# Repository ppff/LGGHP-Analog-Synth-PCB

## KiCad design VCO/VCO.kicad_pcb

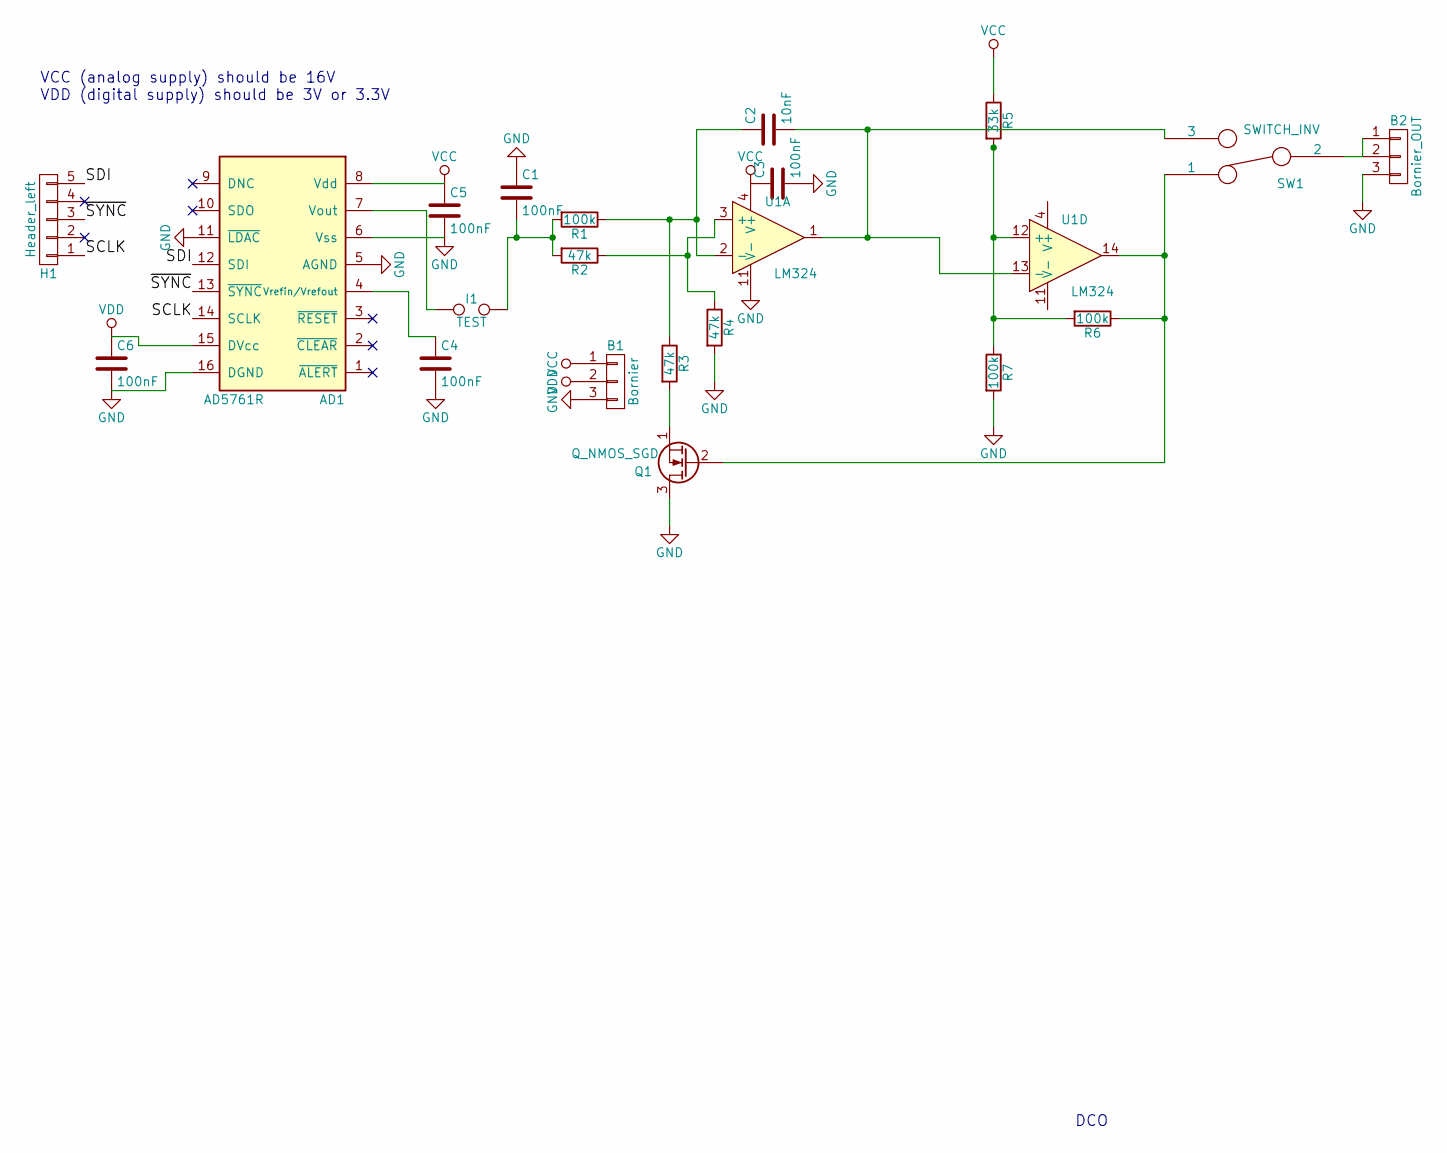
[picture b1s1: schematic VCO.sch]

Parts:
AD1: AD5761R; TSSOP-16_4.4x5mm_Pitch0.65mm
B1: Bornier; Bornier_3pins
B2: Bornier_OUT; Bornier_3pins
C1, C3, C4, C5, C6: 100nF; C_Axial_L5.1mm_D3.1mm_P7.50mm_Horizontal
C2: 10nF; C_Axial_L5.1mm_D3.1mm_P7.50mm_Horizontal
H1: Header_left; Pin_Header_Straight_1x05_Pitch2.54mm
I1: TEST; test
Q1: Q_NMOS_SGD; TO-92_Inline_Wide
R1, R6, R7: 100k; R_Axial_DIN0207_L6.3mm_D2.5mm_P7.62mm_Horizontal
R2, R3, R4: 47k; R_Axial_DIN0207_L6.3mm_D2.5mm_P7.62mm_Horizontal
R5: 33k; R_Axial_DIN0207_L6.3mm_D2.5mm_P7.62mm_Horizontal
SW1: SWITCH_INV; switch
U1: LM324; DIP-14_W7.62mm

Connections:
/SCLK: AD1.14 (SCLK), H1.1
/SDI: AD1.12 (SDI), H1.5
/~SYNC: AD1.13 (~SYNC), H1.3
GND: AD1.5 (AGND), AD1.6 (Vss), AD1.11 (~LDAC), AD1.16 (DGND), B1.3, B2.3, C1.1, C3.2, C4.2, C5.2, C6.2, Q1.3 (D), R4.2, R7.2, U1.11 (V-)
unnamed: AD1.4 (Vrefin/Vrefout), C4.1
unnamed: AD1.7 (Vout), I1.1
unnamed: B2.1, B2.2, SW1.2
unnamed: C1.2, I1.2, R1.2, R2.2
unnamed: C2.1, R1.1, R3.1, U1.2 (-)
unnamed: C2.2, SW1.3, U1.1, U1.13 (-)
unnamed: Q1.1 (S), R3.2
unnamed: Q1.2 (G), R6.1, SW1.1, U1.14
unnamed: R2.1, R4.1, U1.3 (+)
unnamed: R5.2, R6.2, R7.1, U1.12 (+)
VCC: AD1.8 (Vdd), B1.1, C3.1, C5.1, R5.1, U1.4 (V+)
VDD: AD1.15 (DVcc), B1.2, C6.1

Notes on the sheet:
DCO
VCC (analog supply) should be 16V VDD (digital supply) should be 3V or 3.3V

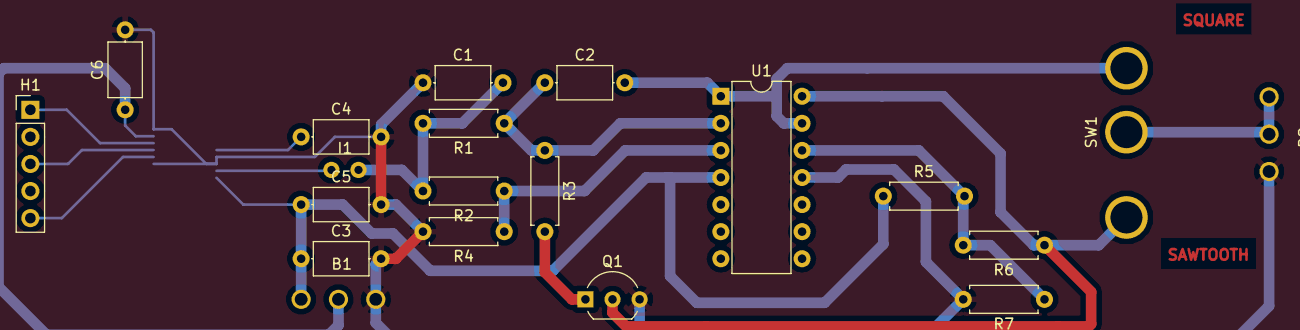
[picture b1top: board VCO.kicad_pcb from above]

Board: 2 copper layers, 21 parts (1 on the bottom side), 16 nets.

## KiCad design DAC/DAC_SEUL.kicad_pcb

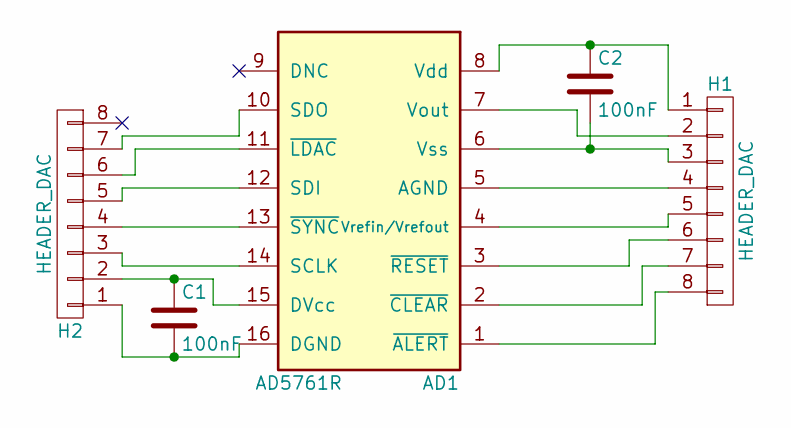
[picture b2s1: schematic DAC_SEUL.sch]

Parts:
AD1: AD5761R; TSSOP-16_4.4x5mm_Pitch0.65mm
C1, C2: 100nF; C_Axial_L5.1mm_D3.1mm_P7.50mm_Horizontal
H1, H2: HEADER_DAC; Pin_Header_Straight_1x08_Pitch2.54mm

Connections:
unnamed: AD1.1 (~ALERT), H1.8
unnamed: AD1.2 (~CLEAR), H1.7
unnamed: AD1.3 (~RESET), H1.6
unnamed: AD1.4 (Vrefin/Vrefout), H1.5
unnamed: AD1.5 (AGND), H1.4
unnamed: AD1.6 (Vss), C2.2, H1.3
unnamed: AD1.7 (Vout), H1.2
unnamed: AD1.8 (Vdd), C2.1, H1.1
unnamed: AD1.10 (SDO), H2.7
unnamed: AD1.11 (~LDAC), H2.6
unnamed: AD1.12 (SDI), H2.5
unnamed: AD1.13 (~SYNC), H2.4
unnamed: AD1.14 (SCLK), H2.3
unnamed: AD1.15 (DVcc), C1.1, H2.2
unnamed: AD1.16 (DGND), C1.2, H2.1

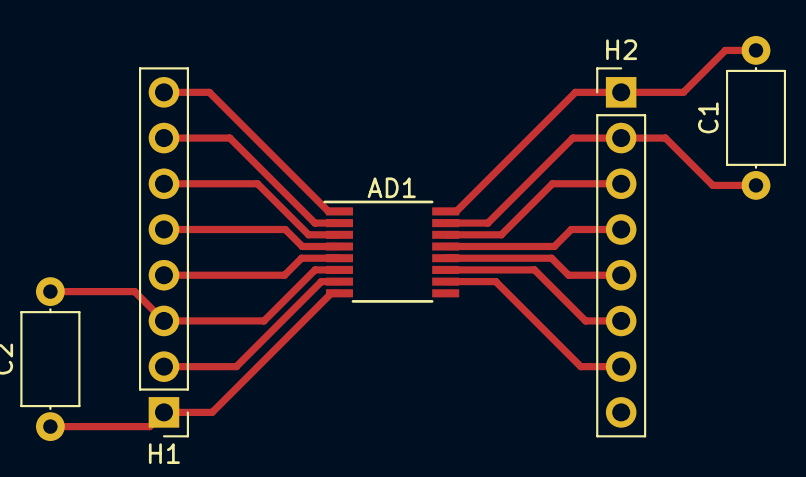
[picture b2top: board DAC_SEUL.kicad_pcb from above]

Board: 2 copper layers, 5 parts (0 on the bottom side), 15 nets.

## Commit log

2017-03-21 VCO Kicad
2017-03-28 VCO + DAC V2
2017-03-28 Cleaned power supplies
2017-04-05 VCO maJ
2017-04-05 DAC seul
2017-04-12 VCO avec empreintes
2017-04-13 Routage fait / petit défaut
2017-04-14 Fixed AO power
2017-04-14 DCO final version
2017-04-21 Added labels and fixed routing
2017-04-27 Fixed VCO
